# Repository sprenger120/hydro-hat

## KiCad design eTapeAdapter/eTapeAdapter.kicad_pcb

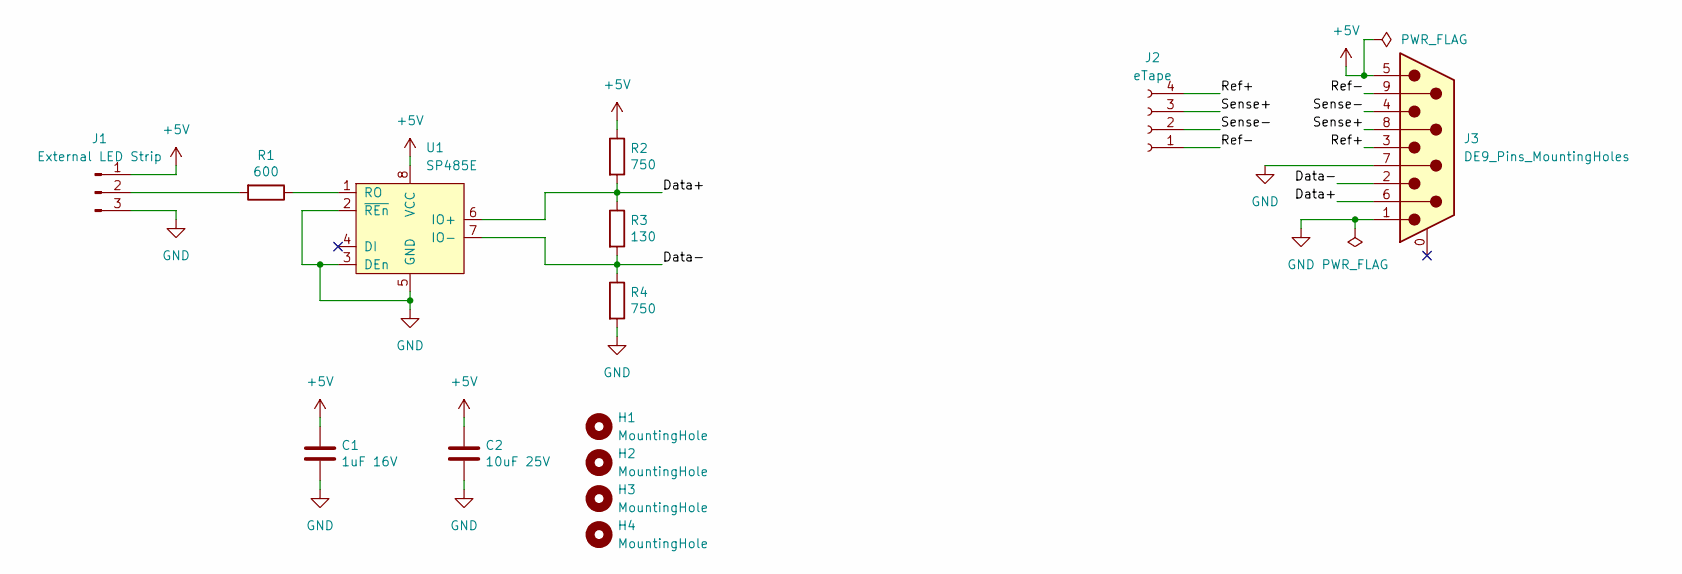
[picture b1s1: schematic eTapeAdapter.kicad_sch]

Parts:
C1: 1uF 16V; C_0603_1608Metric_Pad1.08x0.95mm_HandSolder
C2: 10uF 25V; C_0805_2012Metric_Pad1.18x1.45mm_HandSolder
H1, H2, H3, H4: MountingHole; MountingHole_3.2mm_M3
J1: External LED Strip; PinHeader_1x03_P2.54mm_Vertical
J2: eTape; PinSocket_1x04_P2.54mm_Horizontal
J3: DE9_Pins_MountingHoles; DSUB-9_Pins_Horizontal_P2.77x2.84mm_EdgePinOffset9.90mm_Hou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
R1: 600; R_0603_1608Metric_Pad0.98x0.95mm_HandSolder
R2, R4: 750; R_0603_1608Metric_Pad0.98x0.95mm_HandSolder
R3: 130; R_0603_1608Metric_Pad0.98x0.95mm_HandSolder
U1: SP485E; SOIC-8_3.9x4.9mm_P1.27mm

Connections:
+5V: C1.1, C2.1, J1.1, J3.5, R2.1, U1.8 (VCC)
/Data+: J3.6, R2.2, R3.1, U1.6 (IO+)
/Data-: J3.2, R3.2, R4.1, U1.7 (IO-)
/Ref+: J2.4, J3.3
/Ref-: J2.1, J3.9
/Sense+: J2.3, J3.8
/Sense-: J2.2, J3.4
GND: C1.2, C2.2, J1.3, J3.1, J3.7, R4.2, U1.2 (~REn), U1.3 (DEn), U1.5 (GND)
unnamed: J1.2, R1.2
unnamed: R1.1, U1.1 (RO)

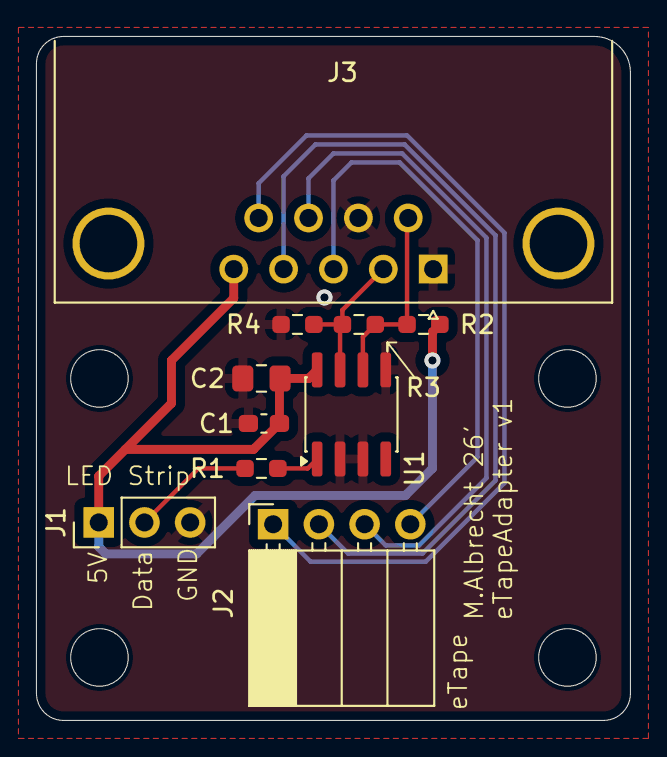
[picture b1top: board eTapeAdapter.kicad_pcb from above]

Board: 2 copper layers, 33.0 x 38.0 mm, 14 parts (0 on the bottom side), 10 nets.

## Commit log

2026-02-03 Basic connector placement, notes, todos
2026-02-05 Specified fuses, selected connectors, selected adc
    - 3.3V, 5V fuse spec for raspi from pinout.xyz
    - de9 connector for eTapes (shielded + cheap)
    - ad7298 adc, easily available
2026-02-07 notes about optocoupling
2026-02-07 added spice model for exploring wheatstone bridges
2026-02-12 Ignored temporary LTspice files
2026-02-12 Changed wheatstone simulation to use Analog Devices approach to linearization
2026-02-12 Notes added by 'git notes add'
2026-02-24 Added new PCB: eTape Adapter Connects to eTape continuous liquid level sensor to a DB9 Connector Also contains rs485 receiver, power for 5V addressible led strip Will function as indicator when tanks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
